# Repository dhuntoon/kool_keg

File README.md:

# Kool Keg
Purdue University > ECE Senior Design (ECE 49022) > Lab Section 5 > Team 51

This repository holds relevant files for Team 51 (_Kool Keg_) in ECE Senior Design. It includes hardware schematics, PCB layouts, mobile application software, and software diagrams.

## Table of Contents

kool_keg (repository home directory)

* `/Circuit Design/...`
  * system hardware schematics
  
* `/main/...`
  * Software for MCU
 
* `/Kool Keg Circuit/...`
  * PCB Design and related files for system hardware

* `/Software/...`
  * Software subsystem working directory
  * `/aws_backend/...`
    * sub-directory contianing AWS Lambda code . 
    * This code is mirrored manually for reference and is **not** executed directly from this source.
    * **This directory holds code written by Dylan Huntoon for the subsystem**
  * `/figures/`...
    * sub-directory containing software flow diagrams and subsystem block diagram(s)
    * **This directory holds figures created by Dylan Huntoon for the subsystem**
  * `/keg_app/...`
    * sub-directory containing code related to the mobile app (Flutter SDK and dependencies)
    * `/lib/...`
      * sub-directory containing Flutter (Dart) code for the mobile app
      * **This directory holds code written by Dylan Huntoon for the subsystem**
  * `/testing_scripts/...` 
    * sub-directory containing Python code and JSON output for testing the software_subsystem
    * **This directory holds code written by Dylan Huntoon for the subsystem**
 
* `/README.md`
  * this markdown file

## Software Design

### Subsystem Block Diagram
The following diagram illustrates the components of the software subsystem and related interactions with other subsystems. The color-coding corresponds to the overall system diagram, found in the design documentation.

### Subsystem Software Architecture
The following diagram illustrates the software architecture for the system's mobile application. The program is written in Flutter (Dart) and is deployable on iOS and Android platforms. The black circle identifies the program entry point and is triggered when the application launches. 

For further detail, see the related figures in the `Software/figures/` subdirectory.

## Operating the Mobile App

Updated Nov 1, 2022.

The mobile application will be deployed onto devices supporting the iOS and Android platforms. Execution will automatically begin when the application is launched on the aforementioned devices.

To build or prototype with the program on a local machine, you must install the following dependencies. To ensure dependencies are installed correctly, reference the flutter documentation (https://docs.flutter.dev/get-started/install).

Dependencies:
* Flutter (Flutter SDK 3.3.1)
* Android toolchain (Android SDK version 33.0.0)
* Xcode (Xcode 14.0) - for building and emulating iOS applications
* Android Studio (version 2021.2) - for emulating Android applications

For rapid prototyping and testing, an IDE (such as VSCode or XCode) is recommended. Alternative command line operations are listed below for Unix terminals. 

### Command Line Operations

See the following documentation for Flutter Command Line Tools: https://docs.flutter.dev/reference/flutter-cli.

```$ flutter --version``` returns the version of flutter installed on your machine. 

```$ flutter doctor``` returns the dependency checks for the aforementioned libraries. Helpful installation directions are provided for missing dependencies. 

To build the program:
```
$ cd kool_keg/Software/keg_app
$ flutter build target
```
where `target` is the targeted platform (ios, android, etc.)

To run the program:
```
$ cd kool_keg/Software/keg_app
$ flutter run lib/main.dart
```

## Credits

Contributors to this repository:
* Cole Kniffen (ckniffen@purdue.edu)
* Dylan Huntoon (dhuntoon@purdue.edu)
* Mitchell Morris (morri448@purdue.edu)
* Jared Nutt (nuttj@purdue.edu)

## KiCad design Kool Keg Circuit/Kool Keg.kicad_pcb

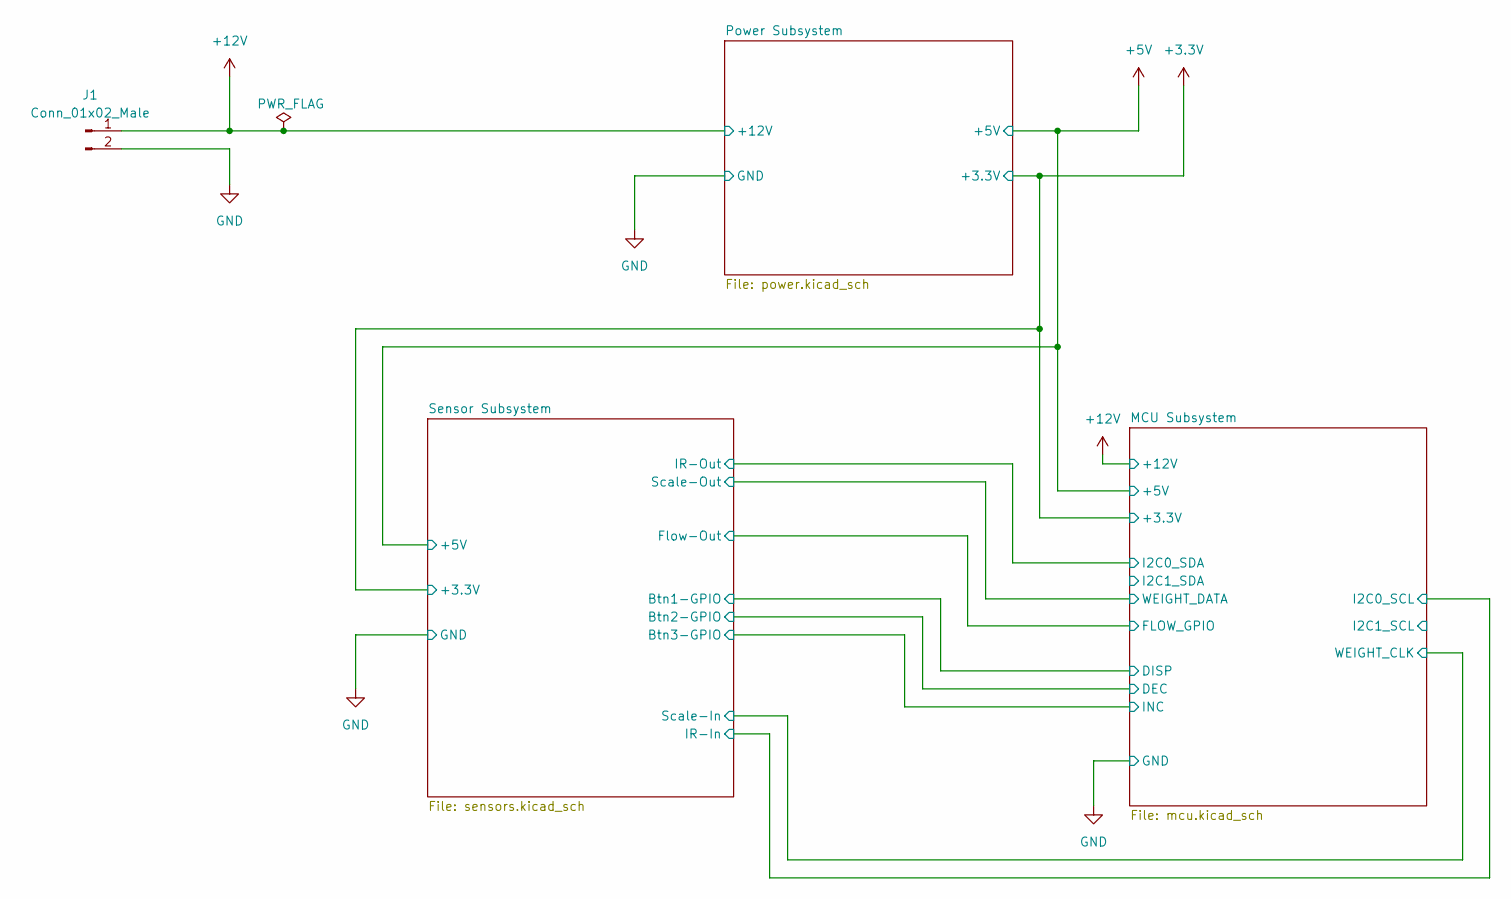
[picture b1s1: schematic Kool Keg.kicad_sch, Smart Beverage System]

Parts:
J1: Conn_01x02_Male; Molex_KK-396_A-41791-0002_1x02_P3.96mm_Vertical

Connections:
+12V: J1.1; also elsewhere on the board
GND: J1.2; also elsewhere on the board

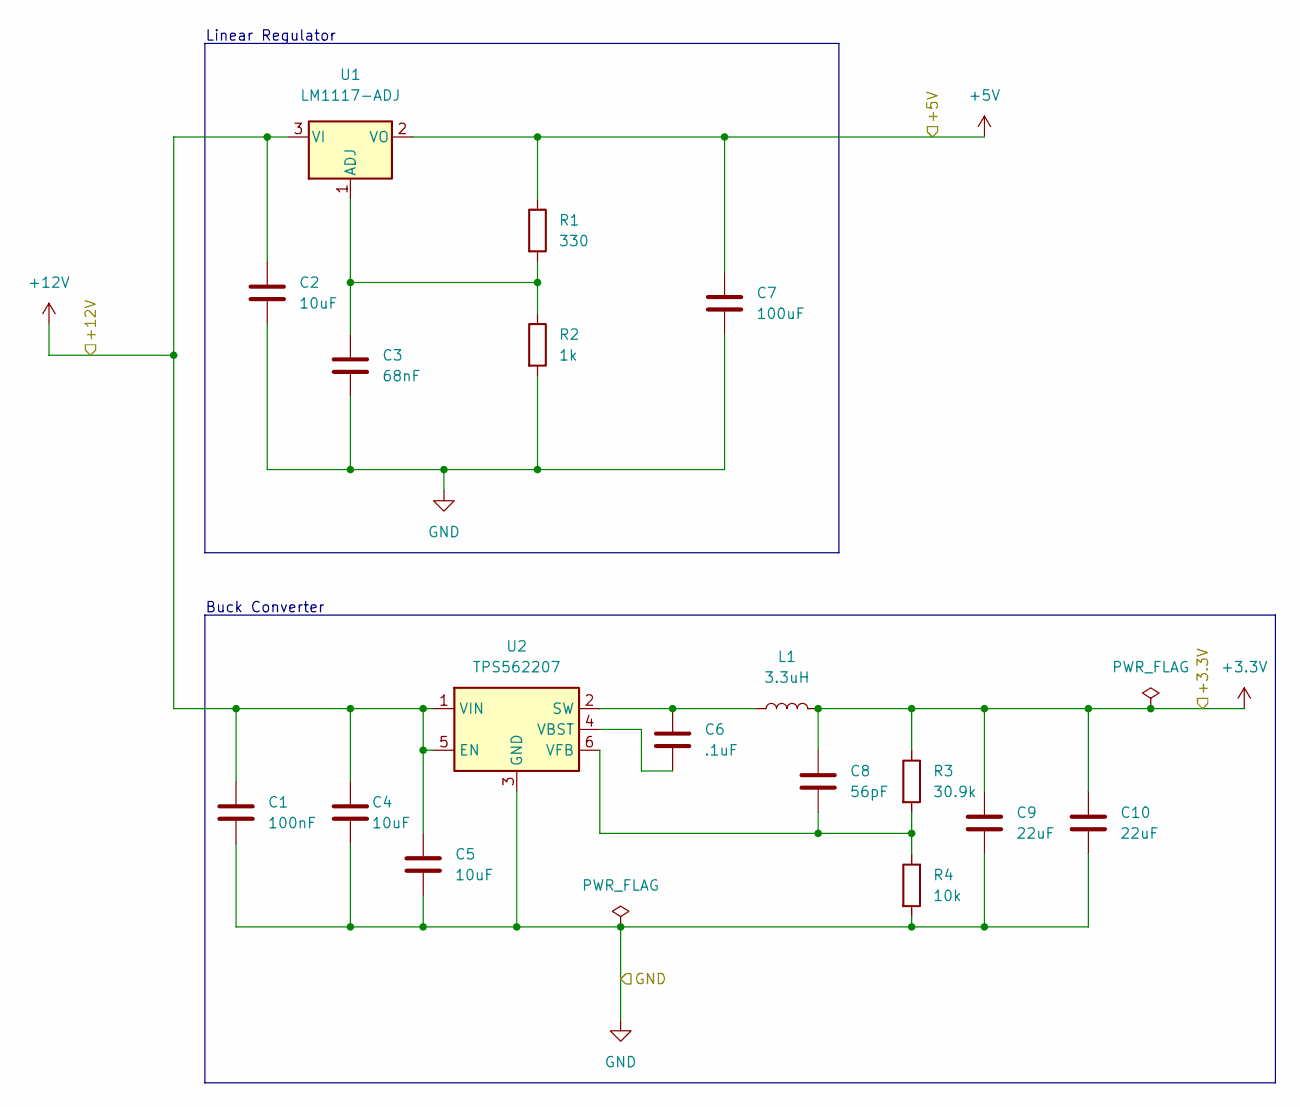
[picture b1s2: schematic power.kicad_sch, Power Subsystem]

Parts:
C1: 100nF; C_0805_2012Metric_Pad1.18x1.45mm_HandSolder
C2: 10uF; CP_Elec_4x5.8
C3: 68nF; C_0805_2012Metric_Pad1.18x1.45mm_HandSolder
C4, C5: 10uF; C_0805_2012Metric_Pad1.18x1.45mm_HandSolder
C6: .1uF; C_0805_2012Metric_Pad1.18x1.45mm_HandSolder
C7: 100uF; CP_Elec_6.3x5.8
C8: 56pF; C_0603_1608Metric_Pad1.08x0.95mm_HandSolder
C9, C10: 22uF; C_0805_2012Metric_Pad1.18x1.45mm_HandSolder
L1: 3.3uH; L_Bourns_SRN6045TA
R1: 330; R_0805_2012Metric_Pad1.20x1.40mm_HandSolder
R2: 1k; R_0805_2012Metric_Pad1.20x1.40mm_HandSolder
R3: 30.9k; R_0805_2012Metric_Pad1.20x1.40mm_HandSolder
R4: 10k; R_0805_2012Metric_Pad1.20x1.40mm_HandSolder
U1: LM1117-ADJ; SOT-223-3_TabPin2
U2: TPS562207; SOT-563

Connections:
+3.3V: C8.1, C9.1, C10.1, L1.2, R3.1; also elsewhere on the board
+5V: C7.1, R1.1, U1.2 (VO); also elsewhere on the board
+12V: C1.1, C2.1, C4.1, C5.1, U1.3 (VI), U2.1 (VIN), U2.5 (EN); also elsewhere on the board
GND: C1.2, C2.2, C3.2, C4.2, C5.2, C7.2, C9.2, C10.2, R2.2, R4.2, U2.3 (GND); also elsewhere on the board
unnamed: C3.1, R1.2, R2.1, U1.1 (ADJ)
unnamed: C6.1, L1.1, U2.2 (SW)
unnamed: C6.2, U2.4 (VBST)
unnamed: C8.2, R3.2, R4.1, U2.6 (VFB)

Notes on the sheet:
Buck Converter
Linear Regulator

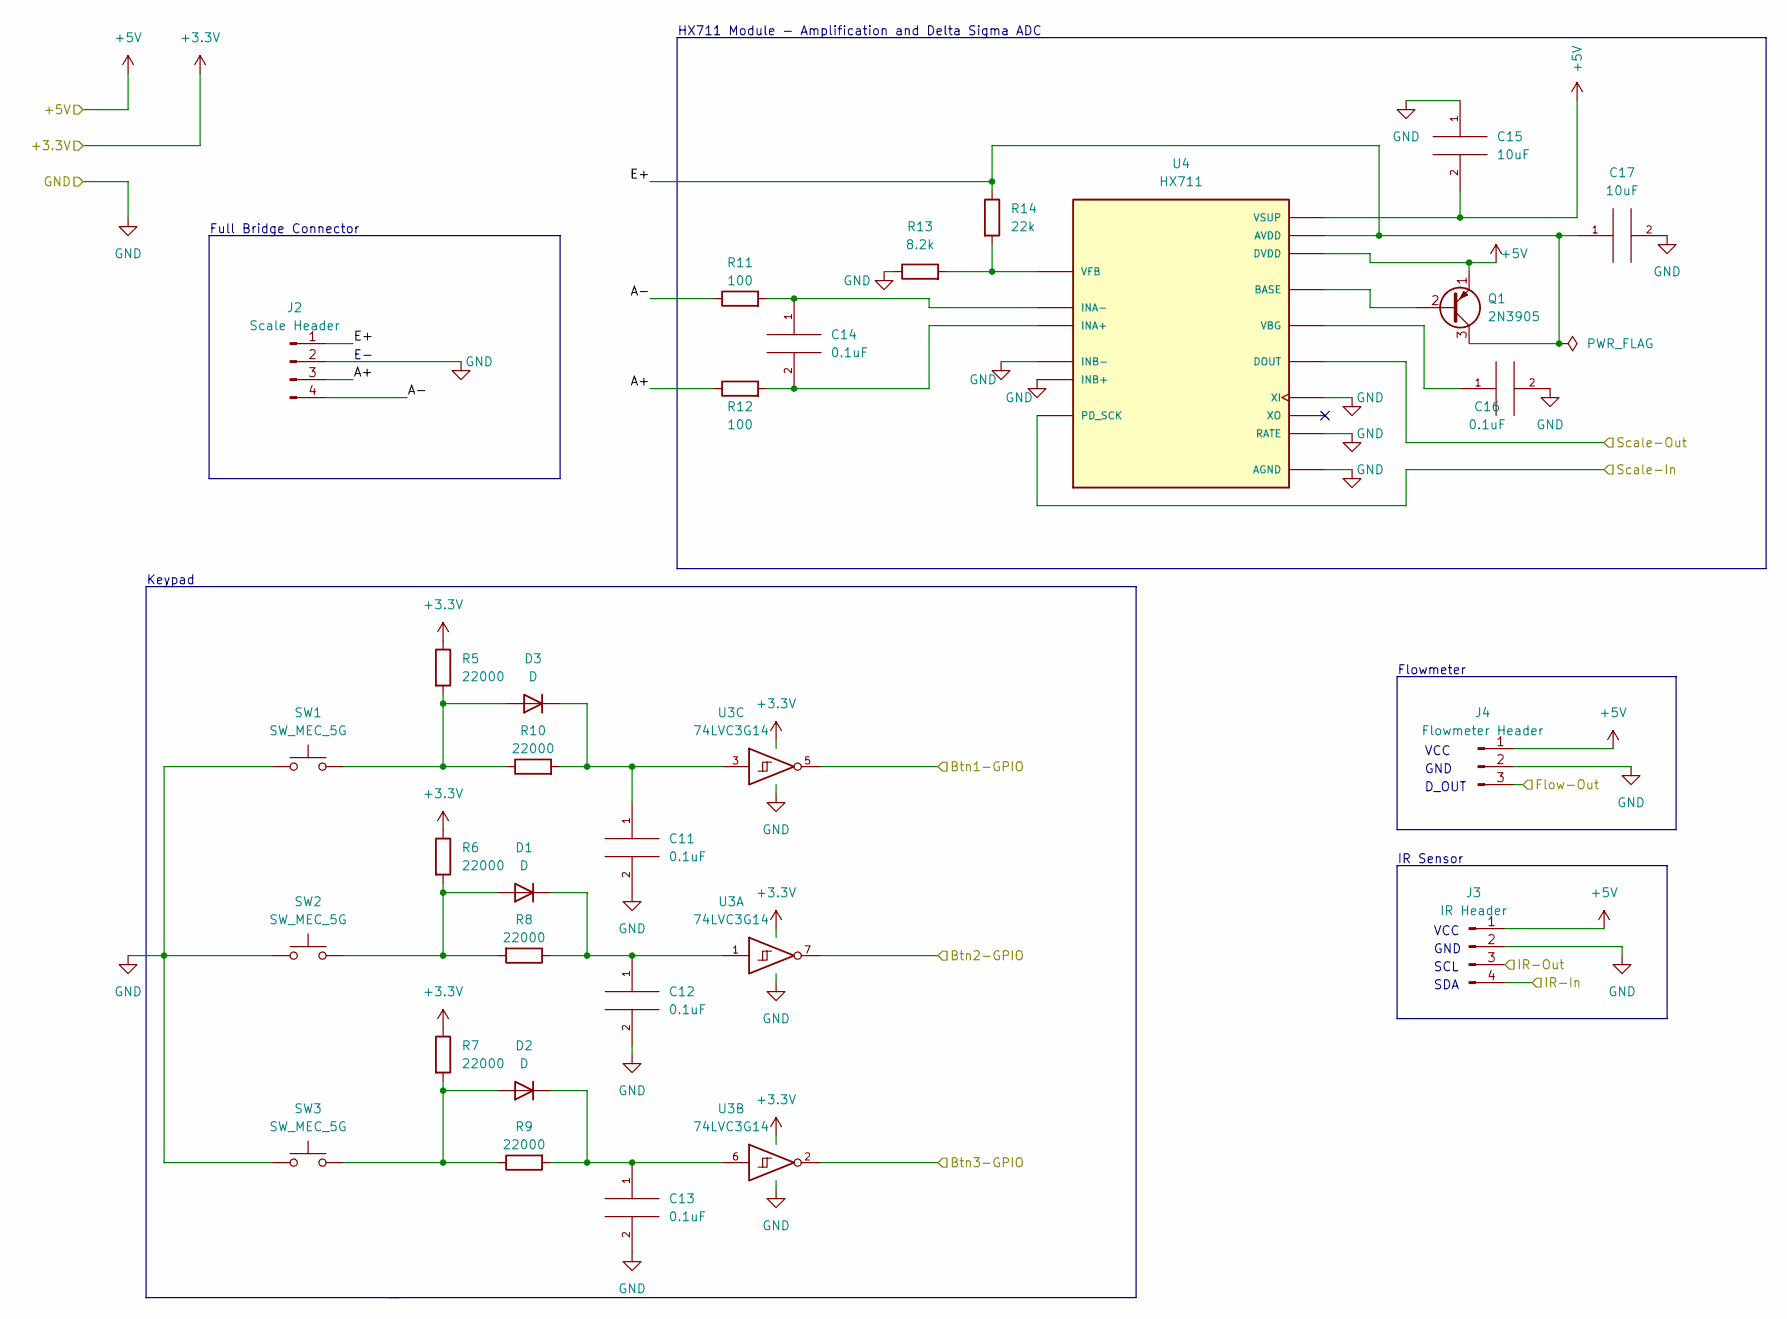
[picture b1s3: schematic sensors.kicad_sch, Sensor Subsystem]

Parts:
C11, C12, C13, C14, C16: 0.1uF; C_0805_2012Metric_Pad1.18x1.45mm_HandSolder
C15, C17: 10uF; C_0805_2012Metric_Pad1.18x1.45mm_HandSolder
D1, D2, D3: D; D_SOD-323_HandSoldering
J2: Scale Header; PinHeader_1x04_P2.00mm_Vertical
J3: IR Header; PinHeader_1x04_P2.00mm_Vertical
J4: Flowmeter Header; PinHeader_1x03_P2.00mm_Vertical
Q1: 2N3905; TO-92_Inline
R5, R6, R7, R8, R9, R10: 22000; R_0805_2012Metric_Pad1.20x1.40mm_HandSolder
R11, R12: 100; R_0805_2012Metric_Pad1.20x1.40mm_HandSolder
R13: 8.2k; R_0805_2012Metric_Pad1.20x1.40mm_HandSolder
R14: 22k; R_0805_2012Metric_Pad1.20x1.40mm_HandSolder
SW1, SW2, SW3: SW_MEC_5G; SW_PUSH-12mm
U3: 74LVC3G14; MSOP-8_3x3mm_P0.65mm
U4: HX711; SOP-16_3.9x9.9mm_P1.27mm; PARTREV V2.0

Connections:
+3.3V: R5.1, R6.1, R7.1, U3.8 (VCC); also elsewhere on the board
+5V: C15.2, J3.1, J4.1, Q1.1 (E), U4.1 (VSUP), U4.16 (DVDD); also elsewhere on the board
/MCU Subsystem/DEC: U3.7; also elsewhere on the board
/MCU Subsystem/DISP: U3.5; also elsewhere on the board
/MCU Subsystem/FLOW_GPIO: J4.3; also elsewhere on the board
/MCU Subsystem/I2C0_SCL: J3.4; also elsewhere on the board
/MCU Subsystem/I2C0_SDA: J3.3; also elsewhere on the board
/MCU Subsystem/INC: U3.2; also elsewhere on the board
/MCU Subsystem/WEIGHT_CLK: U4.11 (PD_SCK); also elsewhere on the board
/MCU Subsystem/WEIGHT_DATA: U4.12 (DOUT); also elsewhere on the board
/Sensor Subsystem/A+: J2.3, R12.1
/Sensor Subsystem/A-: J2.4, R11.1
/Sensor Subsystem/E+: C17.1, J2.1, Q1.3 (C), R14.1, U4.3 (AVDD)
GND: C11.2, C12.2, C13.2, C15.1, C16.2, C17.2, J2.2, J3.2, J4.2, R13.1, SW1.1, SW2.1, SW3.1, U3.4 (GND), U4.5 (AGND), U4.9 (INB-), U4.10 (INB+), U4.14 (XI), U4.15 (RATE); also elsewhere on the board
unnamed: C11.1, D3.1 (K), R10.2, U3.3
unnamed: C12.1, D1.1 (K), R8.1, U3.1
unnamed: C13.1, D2.1 (K), R9.2, U3.6
unnamed: C14.1, R11.2, U4.7 (INA-)
unnamed: C14.2, R12.2, U4.8 (INA+)
unnamed: C16.1, U4.6 (VBG)
unnamed: D1.2 (A), R6.2, R8.2, SW2.2
unnamed: D2.2 (A), R7.2, R9.1, SW3.2
unnamed: D3.2 (A), R5.2, R10.1, SW1.2
unnamed: Q1.2 (B), U4.2 (BASE)
unnamed: R13.2, R14.2, U4.4 (VFB)

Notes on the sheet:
IR Sensor
GND
D_OUT
VCC
Flowmeter
SDA
HX711 Module - Amplification and Delta Sigma ADC
Full Bridge Connector
SCL
Keypad

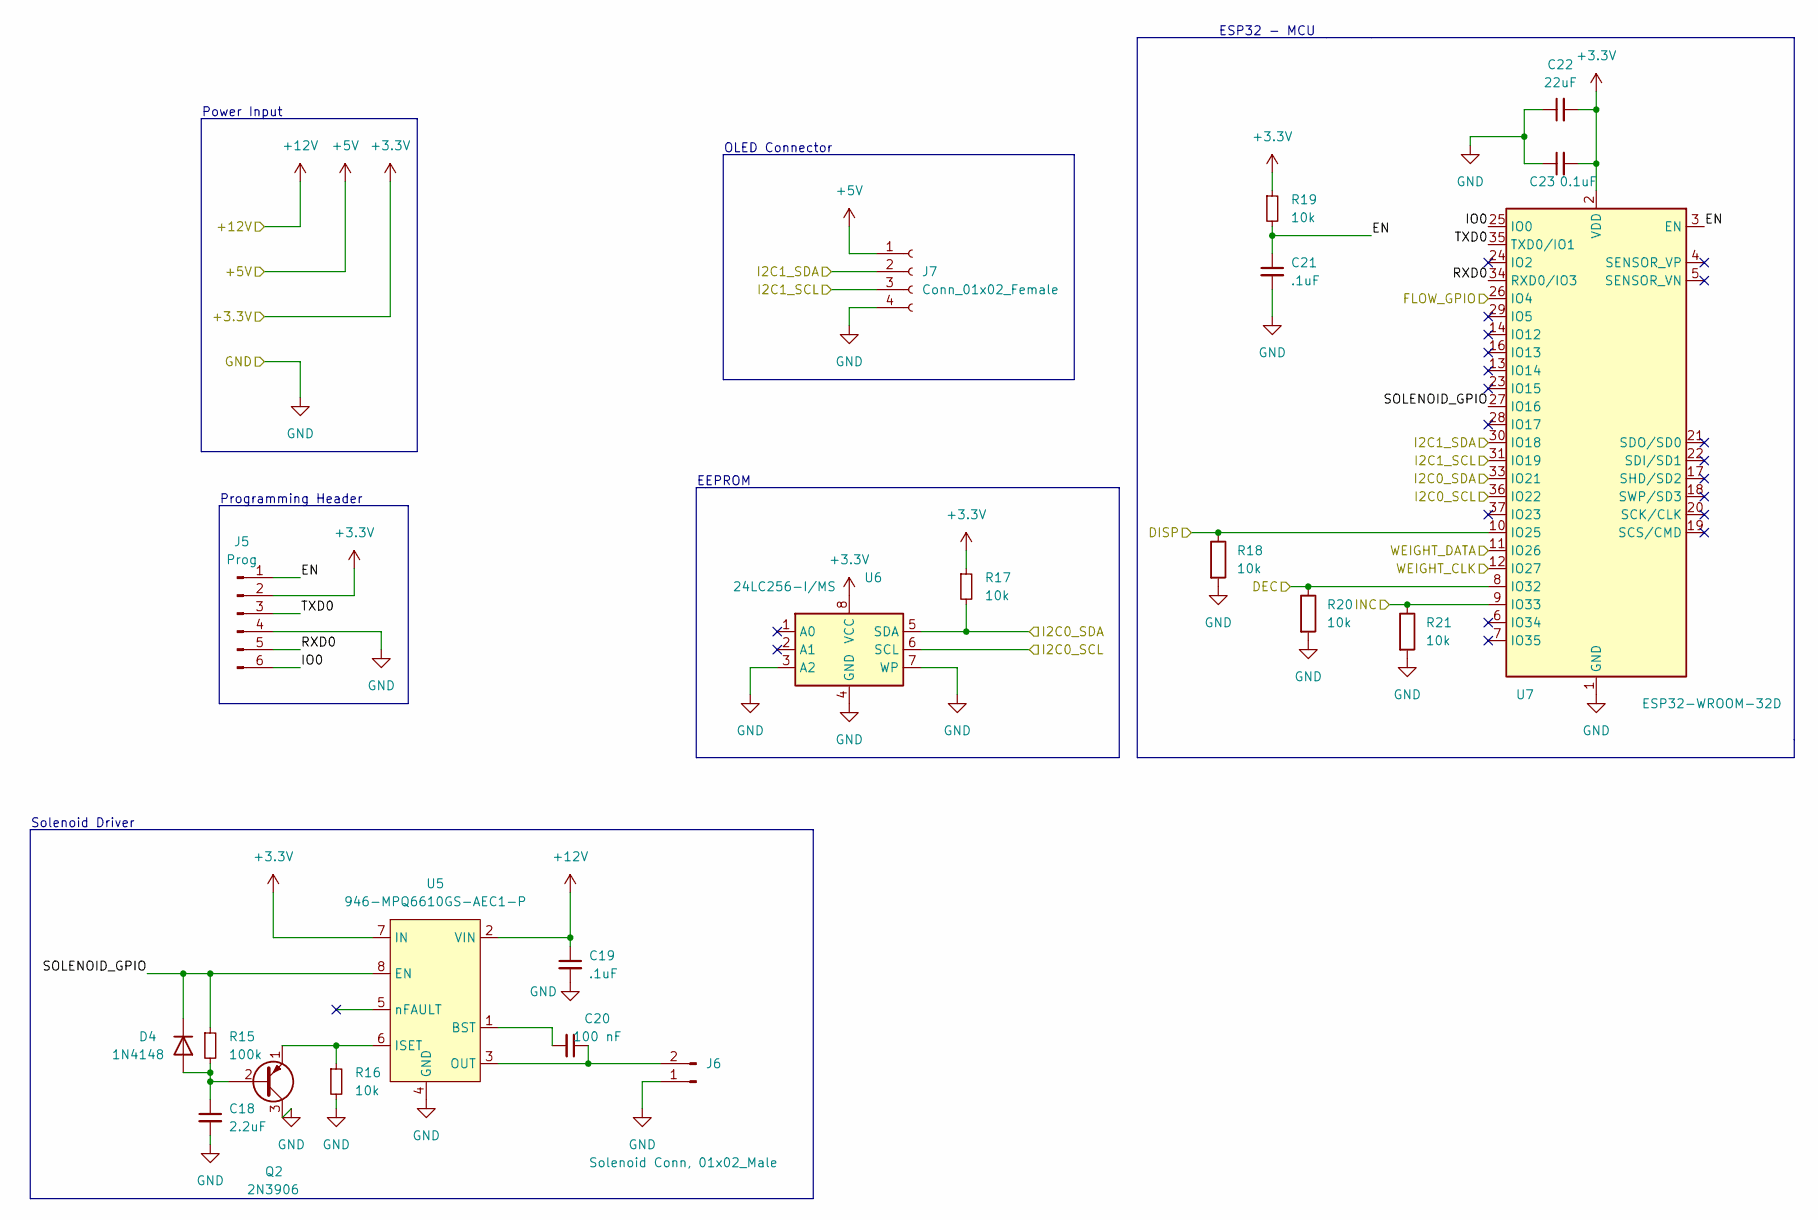
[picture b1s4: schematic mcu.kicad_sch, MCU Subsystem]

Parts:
C18: 2.2uF; C_0805_2012Metric_Pad1.18x1.45mm_HandSolder
C19, C21: .1uF; C_0805_2012Metric_Pad1.18x1.45mm_HandSolder
C20: 100 nF; C_0805_2012Metric_Pad1.18x1.45mm_HandSolder
C22: 22uF; C_0805_2012Metric_Pad1.18x1.45mm_HandSolder
C23: 0.1uF; C_0805_2012Metric_Pad1.18x1.45mm_HandSolder
D4: 1N4148; D_DO-35_SOD27_P7.62mm_Horizontal
J5: Prog; PinHeader_1x06_P2.00mm_Vertical
J6: Solenoid Conn, 01x02_Male; Molex_KK-396_A-41791-0002_1x02_P3.96mm_Vertical
J7: Conn_01x02_Female; PinHeader_1x04_P2.00mm_Vertical
Q2: 2N3906; TO-92_Inline
R15: 100k; R_0805_2012Metric_Pad1.20x1.40mm_HandSolder
R16, R17, R18, R19, R20, R21: 10k; R_0805_2012Metric_Pad1.20x1.40mm_HandSolder
U5: 946-MPQ6610GS-AEC1-P; SOIC-8_3.9x4.9mm_P1.27mm
U6: 24LC256-I/MS; MSOP-8_3x3mm_P0.65mm
U7: ESP32-WROOM-32D; ESP32-WROOM-32

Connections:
+3.3V: C22.2, C23.2, J5.2, R17.1, R19.1, U5.7 (IN), U6.8 (VCC), U7.2 (VDD); also elsewhere on the board
+5V: J7.1; also elsewhere on the board
+12V: C19.1, U5.2 (VIN); also elsewhere on the board
/MCU Subsystem/DEC: R20.1, U7.8 (IO32); also elsewhere on the board
/MCU Subsystem/DISP: R18.1, U7.10 (IO25); also elsewhere on the board
/MCU Subsystem/EN: C21.1, J5.1, R19.2, U7.3 (EN)
/MCU Subsystem/FLOW_GPIO: U7.26 (IO4); also elsewhere on the board
/MCU Subsystem/I2C0_SCL: U6.6 (SCL), U7.36 (IO22); also elsewhere on the board
/MCU Subsystem/I2C0_SDA: R17.2, U6.5 (SDA), U7.33 (IO21); also elsewhere on the board
/MCU Subsystem/I2C1_SCL: J7.3, U7.31 (IO19)
/MCU Subsystem/I2C1_SDA: J7.2, U7.30 (IO18)
/MCU Subsystem/INC: R21.1, U7.9 (IO33); also elsewhere on the board
/MCU Subsystem/IO0: J5.6, U7.25 (IO0)
/MCU Subsystem/RXD0: J5.5, U7.34 (RXD0/IO3)
/MCU Subsystem/SOLENOID_GPIO: D4.1 (K), R15.1, U5.8 (EN), U7.27 (IO16)
/MCU Subsystem/TXD0: J5.3, U7.35 (TXD0/IO1)
/MCU Subsystem/WEIGHT_CLK: U7.12 (IO27); also elsewhere on the board
/MCU Subsystem/WEIGHT_DATA: U7.11 (IO26); also elsewhere on the board
GND: C18.2, C19.2, C21.2, C22.1, C23.1, J5.4, J6.1, J7.4, Q2.3 (C), R16.2, R18.2, R20.2, R21.2, U5.4 (GND), U6.3 (A2), U6.4 (GND), U6.7 (WP), U7.1 (GND), U7.15 (GND), U7.38 (GND), U7.39 (GND); also elsewhere on the board
unnamed: C18.1, D4.2 (A), Q2.2 (B), R15.2
unnamed: C20.1, J6.2, U5.3 (OUT)
unnamed: C20.2, U5.1 (BST)
unnamed: Q2.1 (E), R16.1, U5.6 (ISET)

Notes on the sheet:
Solenoid Driver
OLED Connector
ESP32 - MCU
Programming Header
Power Input
EEPROM

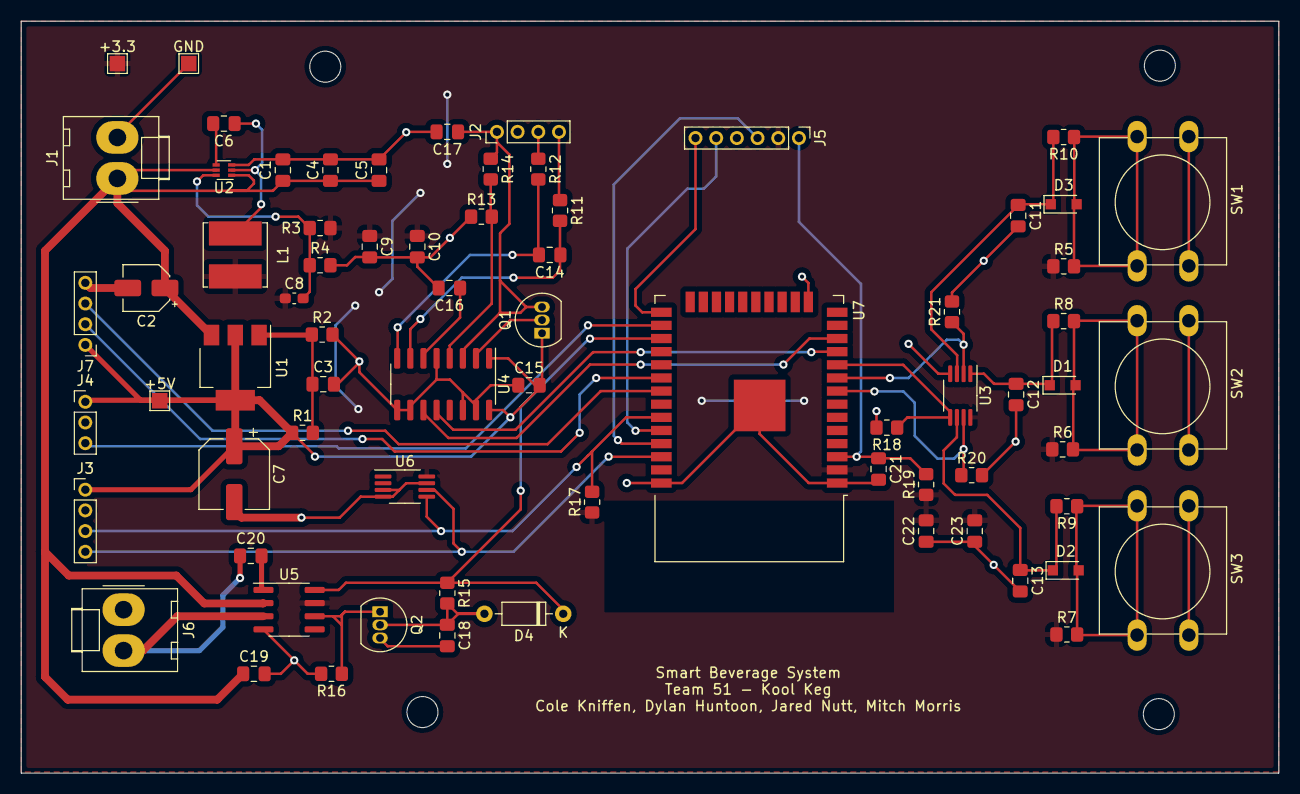
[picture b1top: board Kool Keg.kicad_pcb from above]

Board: 2 copper layers, 121.6 x 72.7 mm, 71 parts (0 on the bottom side), 41 nets.

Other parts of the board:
+3.3, +5V: TestPoint_Pad_1.5x1.5mm
GND: TestPoint_Pad_1.5x1.5mm

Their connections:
+3.3V: +3.3.1; also elsewhere on the board
+5V: +5V.1; also elsewhere on the board
GND: GND.1; also elsewhere on the board

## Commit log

2022-09-13 added app subdirectory
2022-09-13 aws init
2022-09-14 Configured home screen and ListView
2022-09-14 Added Keg object for multi-system support
2022-09-22 Creating combined schem
2022-09-22 Power Sche
2022-09-22 Adding MCU blank sheet and
2022-09-22 removed AWS directories:
    quit
    exit
2022-09-22 rm .DS_Store
2022-09-27 added software figures
2022-09-27 Updated README.md to include figures
2022-09-27 revised Software_design subdirectory filepath
2022-09-27 Update README.md software operation section
2022-09-29 update sensors
2022-09-29 fixed typo in README.md
2022-09-29 added function and in-line documentation
2022-09-29 added function and in-line doc
2022-09-29 Update README.md table of contents
2022-10-04 app now pulls from cloud via http
2022-10-05 http data now displays on app reload
2022-10-12 Update README table of contents to include testing
2022-10-13 Creating hierarch. schem. with combined subsystems
2022-10-13 Rename Top Schmatic.kicad_sch to Updated_Power.kicad_sch
2022-10-13 adding aws keys
2022-10-13 Consolidating yet again
2022-10-13 remove old KiCad project
2022-10-15 Update footprints, init layout
2022-10-17 PCB Layout
2022-10-20 Gerbers, ERC, DRC
2022-10-20 Drill files
2022-10-20 Saving pcb
2022-10-27 copied backend code from aws to repo
2022-10-27 added comments to code for documentation
2022-10-27 added testing script for http put requests
2022-10-27 filename typo: getLambda.py
2022-10-27 aws keys no longer needed
2022-11-01 Update PCB
2022-11-01 PCB update
2022-11-01 gerbers
2022-11-01 organized repo structure for software system
2022-11-18 updated software figures
2022-11-18 Revert "Delete .gitignore"
    This reverts commit 074934398020c8a9fd795506b2b997007f9b18ed.
2022-11-18 Revert "updated software figures"
    This reverts commit 1719d3f3f4208f45d1ca01678667622d50818237.
2022-11-18 update software figures
2022-11-18 removed .gitignore
